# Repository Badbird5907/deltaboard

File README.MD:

# Deltaboard

Deltaboard is a TKL mechanical keyboard, directly using the [Keychron K8](https://www.keychron.com/products/keychron-k8-tenkeyless-wireless-mechanical-keyboard) as inspiration.
The hardest part building this project was routing all the switches and components for the RP2040.

[3D Render](https://autode.sk/4qxmMjt)

## Features:
- TKL Layout
- Kailh MX hotswap sockets
- OLED display
- Integrated RP2040
- USB-C
- RGB lighting
- EC11 Encoder
- QMK/VIA firmware

## Screenshots

### Schematic

### PCB

### Front

### Back

### Case

**Note:** 6mm standoffs are used to keep the keyboard properly fastened to the case. (The height of kailh hotswap sockets are around 5.5mm)

## BOM

| Name                      | Quantity | $ Total (USD) | Notes                                                                 | Links                                                                                                  |
|---------------------------|----------|---------------|-----------------------------------------------------------------------|--------------------------------------------------------------------------------------------------------|
| Cherry MX2A Brown RGB     | 84       | $35.92        | 90x, Free shipping (0.42c/switch)                                     | [Aliexpress](https://www.aliexpress.com/item/1005007917791662.html)                                    |
| DUROCK Stabilizer         | 1        | $8.74         | V3 BS 4x2u 1x6.25u                                                    | [Aliexpress](https://www.aliexpress.com/item/1005006528731543.html)                                    |
| M3 Heat Insert            | 1        | $2.39         | 50x, Free shipping                                                    | [Aliexpress](https://www.aliexpress.com/item/1005003582355741.html)                                    |
| M3 Standoffs (6mm)        | 1        | $2.02         | 50x, Free shipping                                                    | [Aliexpress](https://www.aliexpress.com/item/32539100523.html?spm=a2g0o.productlist.0.0.3351234eJmAx93) |
| M3 Screws (6mm)           | 1        | $1.94         | 50x, Free shipping                                                    | [Aliexpress](https://www.aliexpress.com/item/4001199728978.html)                                       |
| Wormier Pudding Keycaps   | 1        | $17.91        |                                                                       | [Amazon](https://www.amazon.ca/XVX-Keycaps-Universal-Compatiability-Keyboard/)                         |
| Kailh MX Hotswap Sockets  | 90       | $11.35        | 50x + 30x + 10x, Free shipping                                        | [Aliexpress](https://www.aliexpress.com/item/1005007225352311.html)                                    |
| I2C OLED Display (0.91")  | 1        | $2.25         | Free shipping                                                         | [Aliexpress](https://www.aliexpress.com/item/1005005301005280.html)                                    |
| EC11 Rotary Encoders      | 1        | $3.40         | 20mm Half Handle, Free shipping                                       | [Aliexpress](https://www.aliexpress.com/item/1005004907970664.html)                                    |
| Encoder Cap               | 1        | $2.23         | Half Handle Lid, Free shipping                                        | [Aliexpress](https://www.aliexpress.com/item/1005004907970664.html)                                    |
| LCSC Parts                | 1        | $27.33        | $12.47 total, $3 handling fee, $11.86 shipping. Covers MCU, diodes, LEDs | [BOM](https://github.com/Badbird5907/deltaboard/blob/master/Production/PCB/BOM-deltaboard.csv)         |
| PCB                       | 1        | $35.93        | $20.70 PCB + $15.23 shipping                                          |                                                                                                        |
**TOTAL: 151.41 USD**

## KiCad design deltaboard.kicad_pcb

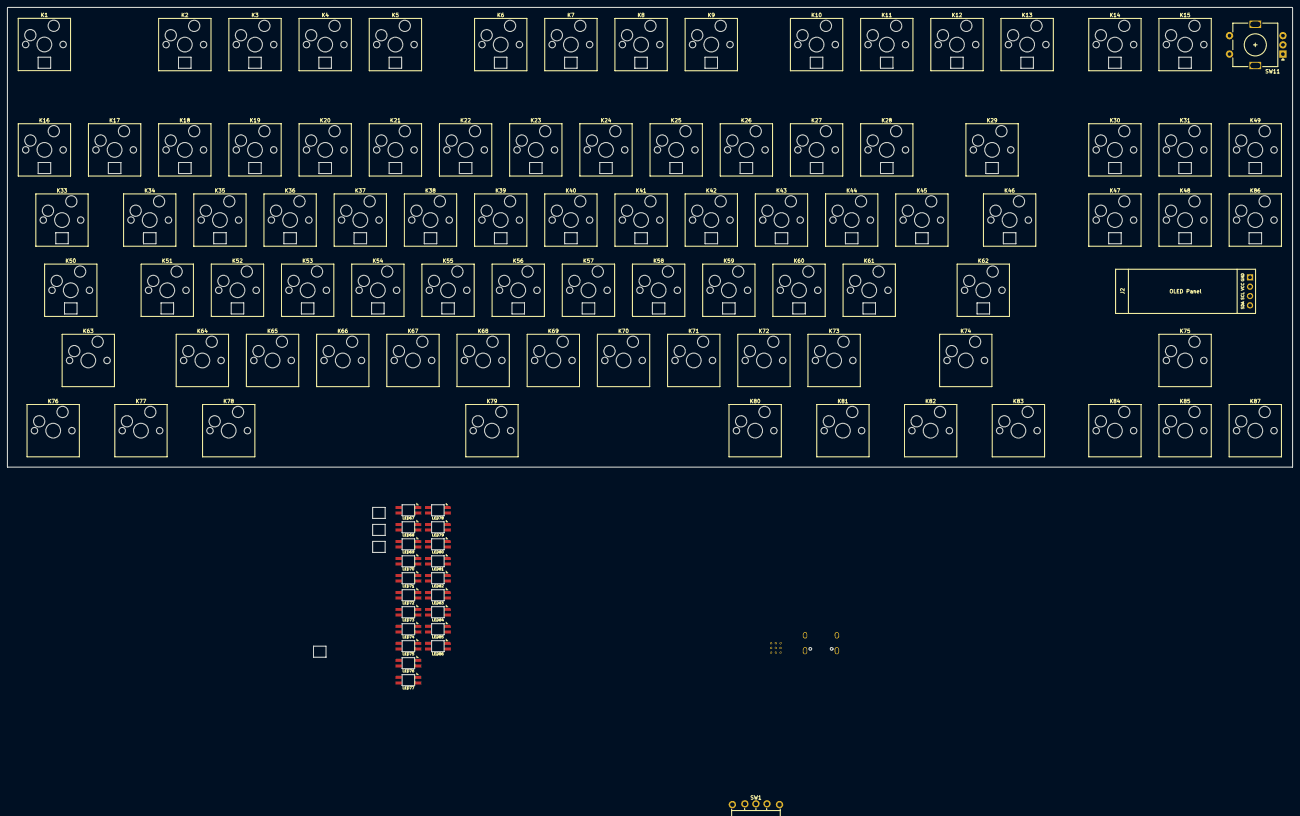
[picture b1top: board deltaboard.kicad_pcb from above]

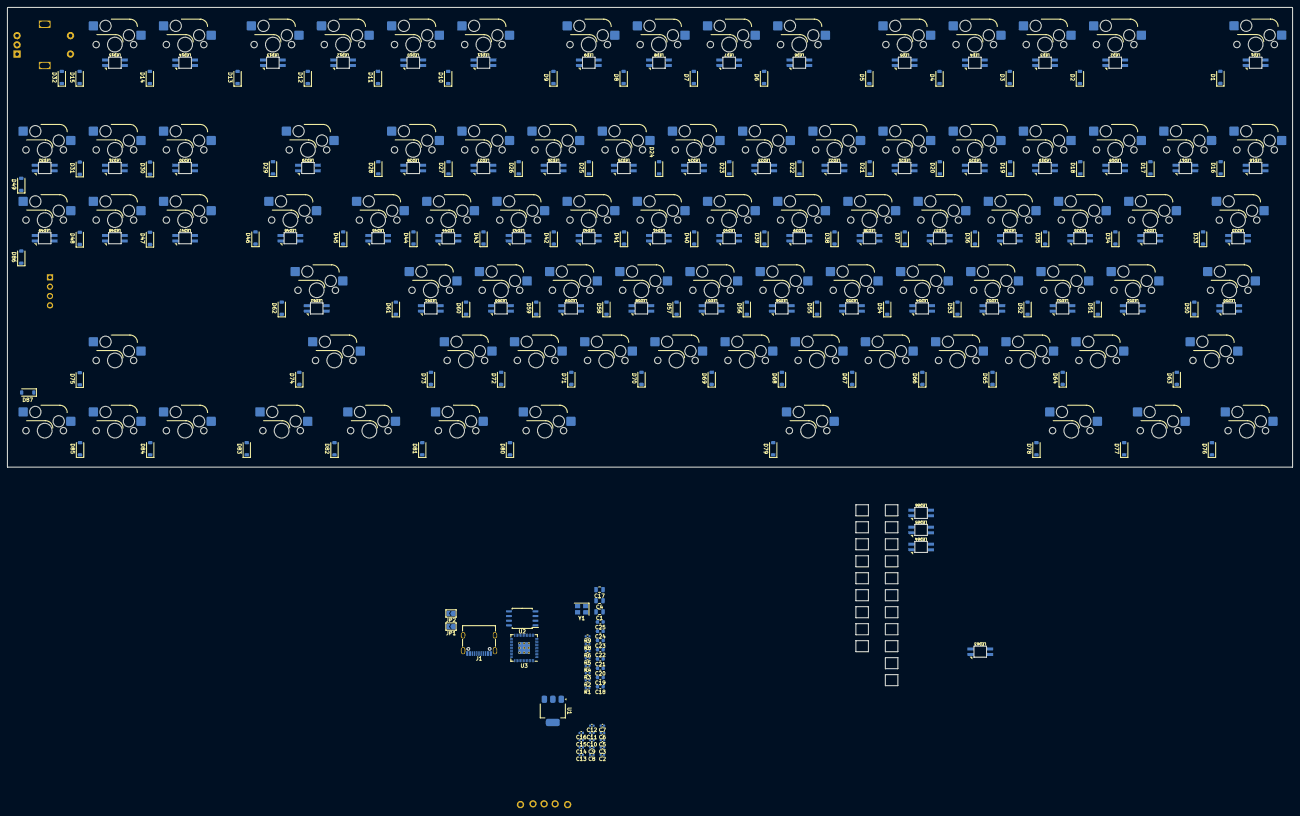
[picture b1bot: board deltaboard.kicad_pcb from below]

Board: 2 copper layers, 348.8 x 184.1 mm, 310 parts (193 on the bottom side), 224 nets, no tracks yet.

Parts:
C1, C4, C17: 10u; C_0805_2012Metric
C2, C3: 15p; C_0402_1005Metric
C5, C6, C7, C9, C11, C12, C13, C14, C15, C16: 100n; C_0402_1005Metric
C8, C10: 1u; C_0402_1005Metric
C18, C19, C20, C21, C22, C23, C24, C25: 2.2uF; C_0603_1608Metric
D1, D2, D3, D4, D5, D6, D7, D8, D9, D10, D11, D12, D13, D14, D15, D16, D17, D18, D19, D20, D21, D22, D23, D24, D25, D26, D27, D28, D29, D30, D31, D32, D33, D34, D35, D36, D37, D38, D39, D40, D41, D42, D43, D44, D45, D46, D47, D48, D49, D50, D51, D52, D53, D54, D55, D56, D57, D58, D59, D60, D61, D62, D63, D64, D65, D66, D67, D68, D69, D70, D71, D72, D73, D74, D75, D76, D77, D78, D79, D80, D81, D82, D83, D84, D85, D86, D87: D; D_SOD-123
H1, H2, H3, H4, H5, H6, H7, H8: MountingHole; MountingHole_2.7mm_M2.5
J1: USB_C_Receptacle; USB-C_SMD-TYPE-C-31-M-12
J2: Conn_01x04; SSD1306-0.91-OLED-4pin-128x32
JP1, JP2: Jumper_2_Open; SolderJumper-2_P1.3mm_Open_TrianglePad1.0x1.5mm
K1: Esc; Hotswap_MX_1.00u
K2: F1; Hotswap_MX_1.00u
K3: F2; Hotswap_MX_1.00u
K4: F3; Hotswap_MX_1.00u
K5: F4; Hotswap_MX_1.00u
K6: F5; Hotswap_MX_1.00u
K7: F6; Hotswap_MX_1.00u
K8: F7; Hotswap_MX_1.00u
K9: F8; Hotswap_MX_1.00u
K10: F9; Hotswap_MX_1.00u
K11: F10; Hotswap_MX_1.00u
K12: F11; Hotswap_MX_1.00u
K13: F12; Hotswap_MX_1.00u
K14, K15: Blank; Hotswap_MX_1.00u
K16: ~~,`; Hotswap_MX_1.00u
K17: !,1; Hotswap_MX_1.00u
K18: @,2; Hotswap_MX_1.00u
K19: #,3; Hotswap_MX_1.00u
K20: $,4; Hotswap_MX_1.00u
K21: %,5; Hotswap_MX_1.00u
K22: ^,6; Hotswap_MX_1.00u
K23: &,7; Hotswap_MX_1.00u
K24: *,8; Hotswap_MX_1.00u
K25: (,9; Hotswap_MX_1.00u
K26: ),0; Hotswap_MX_1.00u
K27: _,-; Hotswap_MX_1.00u
K28: +,=; Hotswap_MX_1.00u
K29: Backspace; Hotswap_MX_2.00u
K30: Insert; Hotswap_MX_1.00u
K31: Home; Hotswap_MX_1.00u
K33: Tab; Hotswap_MX_1.50u
K34: Q; Hotswap_MX_1.00u
K35: W; Hotswap_MX_1.00u
K36: E; Hotswap_MX_1.00u
K37: R; Hotswap_MX_1.00u
K38: T; Hotswap_MX_1.00u
K39: Y; Hotswap_MX_1.00u
K40: U; Hotswap_MX_1.00u
K41: I; Hotswap_MX_1.00u
K42: O; Hotswap_MX_1.00u
K43: P; Hotswap_MX_1.00u
K44: {,[; Hotswap_MX_1.00u
K45: },]; Hotswap_MX_1.00u
K46: |,\; Hotswap_MX_1.50u
K47: Delete; Hotswap_MX_1.00u
K48: End; Hotswap_MX_1.00u
K49: PgUp; Hotswap_MX_1.00u
K50: Caps Lock; Hotswap_MX_1.75u
K51: A; Hotswap_MX_1.00u
K52: S; Hotswap_MX_1.00u
K53: D; Hotswap_MX_1.00u
K54: F; Hotswap_MX_1.00u
K55: G; Hotswap_MX_1.00u
K56: H; Hotswap_MX_1.00u
K57: J; Hotswap_MX_1.00u
K58: K; Hotswap_MX_1.00u
K59: L; Hotswap_MX_1.00u
K60: :,;; Hotswap_MX_1.00u
K61: ",'; Hotswap_MX_1.00u
K62: Enter; Hotswap_MX_2.25u
K63: Shift; Hotswap_MX_2.25u
K64: Z; Hotswap_MX_1.00u
K65: X; Hotswap_MX_1.00u
K66: C; Hotswap_MX_1.00u
K67: V; Hotswap_MX_1.00u
K68: B; Hotswap_MX_1.00u
K69: N; Hotswap_MX_1.00u
K70: M; Hotswap_MX_1.00u
K71: <,,; Hotswap_MX_1.00u
K72: >,.; Hotswap_MX_1.00u
K73: ?,/; Hotswap_MX_1.00u
K74: Shift; Hotswap_MX_2.75u
K75: ↑; Hotswap_MX_1.00u
K76, K83: Ctrl; Hotswap_MX_1.25u
K77, K81: Win; Hotswap_MX_1.25u
K78, K80: Alt; Hotswap_MX_1.25u
K79: Blank; Hotswap_MX_6.25u
K82: Menu; Hotswap_MX_1.25u
K84: ←; Hotswap_MX_1.00u
K85: ↓; Hotswap_MX_1.00u
K86: PgDn; Hotswap_MX_1.00u
K87: →; Hotswap_MX_1.00u
LED1, LED2, LED3, LED4, LED5, LED6, LED7, LED8, LED9, LED10, LED11, LED12, LED13, LED14, LED15, LED16, LED17, LED18, LED19, LED20, LED21, LED22, LED23, LED24, LED25, LED26, LED27, LED28, LED29, LED30, LED31, LED32, LED33, LED34, LED35, LED36, LED37, LED38, LED39, LED40, LED41, LED42, LED43, LED44, LED45, LED46, LED47, LED48, LED49, LED50, LED51, LED52, LED53, LED54, LED55, LED56, LED57, LED58, LED59, LED60, LED61, LED62, LED63, LED64, LED65, LED66, LED67, LED68, LED69, LED70, LED71, LED72, LED73, LED74, LED75, LED76, LED77, LED78, LED79, LED80, LED81, LED82, LED83, LED84, LED85, LED86: SK6812-MINI-E; SK6812MINI-E
R1, R5, R6: 1k; R_0402_1005Metric
R2: DNF; R_0402_1005Metric
R3, R4: 27; R_0402_1005Metric
R8, R9: 5.1k; R_0402_1005Metric
SW1: SW_SPST; SW-TH_KH-SS12F23-G6
SW11: RotaryEncoder_Switch; encoder
U1: NCP1117-3.3_SOT223; SOT-223-3_TabPin2
U2: W25Q128JVS; SOIC-8_5.23x5.23mm_P1.27mm
U3: RP2040; RP2040-QFN-56
Y1: ABM8-272-T3; Crystal_SMD_3225-4Pin_3.2x2.5mm

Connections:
+1V1: C6.1, C7.1, C8.1, U3.23 (DVDD), U3.45 (VREG_VOUT), U3.50 (DVDD)
+3V3: C4.1, C5.1, C9.1, C10.1, C11.1, C12.1, C13.1, C14.1, C15.1, C16.1, C17.1, R2.1, U1.2 (VO), U2.8 (VCC), U3.1 (IOVDD), U3.10 (IOVDD), U3.22 (IOVDD), U3.33 (IOVDD), U3.42 (IOVDD), U3.43 (ADC_AVDD), U3.44 (VREG_IN), U3.48 (USB_VDD), U3.49 (IOVDD)
/COL_0: K1.1, K16.1, K33.1, K50.1, K63.1, K76.1, U3.8 (GPIO6)
/COL_1: K2.1, K17.1, K34.1, K51.1, K64.1, K77.1, U3.9 (GPIO7)
/COL_2: K3.1, K18.1, K35.1, K52.1, K65.1, K78.1, U3.11 (GPIO8)
/COL_3: K4.1, K19.1, K36.1, K53.1, K66.1, K79.1, U3.12 (GPIO9)
/COL_4: K5.1, K20.1, K37.1, K54.1, K67.1, K80.1, U3.13 (GPIO10)
/COL_5: K6.1, K21.1, K38.1, K55.1, K68.1, K81.1, U3.14 (GPIO11)
/COL_6: K7.1, K22.1, K39.1, K56.1, K69.1, K82.1, U3.15 (GPIO12)
/COL_7: K8.1, K23.1, K40.1, K57.1, K70.1, K83.1, U3.16 (GPIO13)
/COL_8: K9.1, K24.1, K41.1, K58.1, K71.1, K84.1, U3.17 (GPIO14)
/COL_9: K10.1, K25.1, K42.1, K59.1, K72.1, K85.1, U3.18 (GPIO15)
/COL_10: K11.1, K26.1, K43.1, K60.1, K73.1, K87.1, U3.27 (GPIO16)
/COL_11: K12.1, K27.1, K44.1, K61.1, K74.1, U3.28 (GPIO17)
/COL_12: K13.1, K28.1, K45.1, K62.1, K75.1, U3.29 (GPIO18)
/COL_13: K14.1, K29.1, K46.1, U3.30 (GPIO19)
/COL_14: K15.1, K30.1, K47.1, U3.31 (GPIO20)
/COL_16: K49.1, K86.1, U3.34 (GPIO22)
/GPIO0: D1.1 (K), D2.1 (K), D3.1 (K), D4.1 (K), D5.1 (K), D6.1 (K), D7.1 (K), D8.1 (K), D9.1 (K), D10.1 (K), D11.1 (K), D12.1 (K), D13.1 (K), D14.1 (K), D15.1 (K), D32.1 (K), U3.2 (GPIO0)
/GPIO1: D16.1 (K), D17.1 (K), D18.1 (K), D19.1 (K), D20.1 (K), D21.1 (K), D22.1 (K), D23.1 (K), D24.1 (K), D25.1 (K), D26.1 (K), D27.1 (K), D28.1 (K), D29.1 (K), D30.1 (K), D31.1 (K), D49.1 (K), U3.3 (GPIO1)
/GPIO2: D33.1 (K), D34.1 (K), D35.1 (K), D36.1 (K), D37.1 (K), D38.1 (K), D39.1 (K), D40.1 (K), D41.1 (K), D42.1 (K), D43.1 (K), D44.1 (K), D45.1 (K), D46.1 (K), D47.1 (K), D48.1 (K), D86.1 (K), U3.4 (GPIO2)
/GPIO3: D50.1 (K), D51.1 (K), D52.1 (K), D53.1 (K), D54.1 (K), D55.1 (K), D56.1 (K), D57.1 (K), D58.1 (K), D59.1 (K), D60.1 (K), D61.1 (K), D62.1 (K), U3.5 (GPIO3)
/GPIO4: D63.1 (K), D64.1 (K), D65.1 (K), D66.1 (K), D67.1 (K), D68.1 (K), D69.1 (K), D70.1 (K), D71.1 (K), D72.1 (K), D73.1 (K), D74.1 (K), D75.1 (K), U3.6 (GPIO4)
/GPIO5: D76.1 (K), D77.1 (K), D78.1 (K), D79.1 (K), D80.1 (K), D81.1 (K), D82.1 (K), D83.1 (K), D84.1 (K), D85.1 (K), D87.1 (K), U3.7 (GPIO5)
/QSPI_SCLK: U2.6 (CLK), U3.52 (QSPI_SCLK)
/QSPI_SD0: U2.5 (DI(IO0)), U3.53 (QSPI_SD0)
/QSPI_SD1: U2.2 (DO(IO1)), U3.55 (QSPI_SD1)
/QSPI_SD2: U2.3 (IO2), U3.54 (QSPI_SD2)
/QSPI_SD3: U2.7 (IO3), U3.51 (QSPI_SD3)
/QSPI_SS: R1.1, R2.2, U2.1 (~CS), U3.56 (QSPI_SS)
/RUN: R6.2, U3.26 (RUN)
/USB_D+: J1.A6 (D+), R3.1
/USB_D-: J1.A7 (D-), R4.1
/XIN: C2.1, U3.20 (XIN), Y1.1
/XOUT: R5.1, U3.21 (XOUT)
/~USB_BOOT: JP1.2 (B), R1.2
ENC_1_A: SW11.A, U3.39 (GPIO27_ADC1)
ENC_1_B: SW11.B, U3.38 (GPIO26_ADC0)
ENC_SWA: D32.2 (A), SW11.S2
ENC_SWB: K31.1, K48.1, SW11.S1, U3.32 (GPIO21)
GND: C1.2, C2.2, C3.2, C4.2, C5.2, C6.2, C7.2, C8.2, C9.2, C10.2, C11.2, C12.2, C13.2, C14.2, C15.2, C16.2, C17.2, C18.2, C19.2, C20.2, C21.2, C22.2, C23.2, C24.2, C25.2, J1.A1 (GND), J1.A12 (GND), J1.B1 (GND), J1.B12 (GND), J2.1, JP1.1 (A), JP2.1 (A), LED1.2 (VSS), LED2.2 (VSS), LED3.2 (VSS), LED4.2 (VSS), LED5.2 (VSS), LED6.2 (VSS), LED7.2 (VSS), LED8.2 (VSS), LED9.2 (VSS), LED10.2 (VSS), LED11.2 (VSS), LED12.2 (VSS), LED13.2 (VSS), LED14.2 (VSS), LED15.2 (VSS), LED16.2 (VSS), LED17.2 (VSS), LED18.2 (VSS), LED19.2 (VSS), LED20.2 (VSS), LED21.2 (VSS), LED22.2 (VSS), LED23.2 (VSS), LED24.2 (VSS), LED25.2 (VSS), LED26.2 (VSS), LED27.2 (VSS), LED28.2 (VSS), LED29.2 (VSS), LED30.2 (VSS), LED31.2 (VSS), LED32.2 (VSS), LED33.2 (VSS), LED34.2 (VSS), LED35.2 (VSS), LED36.2 (VSS), LED37.2 (VSS), LED38.2 (VSS), LED39.2 (VSS), LED40.2 (VSS), LED41.2 (VSS), LED42.2 (VSS), LED43.2 (VSS), LED44.2 (VSS), LED45.2 (VSS), LED46.2 (VSS), LED47.2 (VSS), LED48.2 (VSS), LED49.2 (VSS), LED50.2 (VSS), LED51.2 (VSS), LED52.2 (VSS), LED53.2 (VSS), LED54.2 (VSS), LED55.2 (VSS), LED56.2 (VSS), LED57.2 (VSS), LED58.2 (VSS), LED59.2 (VSS), LED60.2 (VSS), LED61.2 (VSS), LED62.2 (VSS), LED63.2 (VSS), LED64.2 (VSS), LED65.2 (VSS), LED66.2 (VSS), LED67.2 (VSS), LED68.2 (VSS), LED69.2 (VSS), LED70.2 (VSS), LED71.2 (VSS), LED72.2 (VSS), LED73.2 (VSS), LED74.2 (VSS), LED75.2 (VSS), LED76.2 (VSS), LED77.2 (VSS), LED78.2 (VSS), LED79.2 (VSS), LED80.2 (VSS), LED81.2 (VSS), LED82.2 (VSS), LED83.2 (VSS), LED84.2 (VSS), LED85.2 (VSS), LED86.2 (VSS), R8.2, R9.2, SW11.C, U1.1 (GND), U2.4 (GND), U3.19 (TESTEN), U3.57 (GND), Y1.2, Y1.4
I2C_SCL: J2.3, U3.37 (GPIO25)
I2C_SDA: J2.4, U3.36 (GPIO24)
LED: LED1.3 (DIN), U3.35 (GPIO23)
LED_OUT_0: LED15.1 (DOUT), LED16.3 (DIN)
LED_OUT_1: LED32.1 (DOUT), LED33.3 (DIN)
LED_OUT_2: LED49.1 (DOUT), LED50.3 (DIN)
LED_OUT_3: LED62.1 (DOUT), LED63.3 (DIN)
LED_OUT_4: LED75.1 (DOUT), LED76.3 (DIN)
unnamed: C3.1, R5.2, Y1.3
unnamed: D1.2 (A), K1.2
unnamed: D2.2 (A), K2.2
unnamed: D3.2 (A), K3.2
unnamed: D4.2 (A), K4.2
unnamed: D5.2 (A), K5.2
unnamed: D6.2 (A), K6.2
unnamed: D7.2 (A), K7.2
unnamed: D8.2 (A), K8.2
unnamed: D9.2 (A), K9.2
unnamed: D10.2 (A), K10.2
unnamed: D11.2 (A), K11.2
unnamed: D12.2 (A), K12.2
unnamed: D13.2 (A), K13.2
unnamed: D14.2 (A), K14.2
unnamed: D15.2 (A), K15.2
unnamed: D16.2 (A), K16.2
unnamed: D17.2 (A), K17.2
unnamed: D18.2 (A), K18.2
unnamed: D19.2 (A), K19.2
unnamed: D20.2 (A), K20.2
unnamed: D21.2 (A), K21.2
unnamed: D22.2 (A), K22.2
unnamed: D23.2 (A), K23.2
unnamed: D24.2 (A), K24.2
unnamed: D25.2 (A), K25.2
unnamed: D26.2 (A), K26.2
unnamed: D27.2 (A), K27.2
unnamed: D28.2 (A), K28.2
unnamed: D29.2 (A), K29.2
unnamed: D30.2 (A), K30.2
unnamed: D31.2 (A), K31.2
unnamed: D33.2 (A), K33.2
unnamed: D34.2 (A), K34.2
unnamed: D35.2 (A), K35.2
unnamed: D36.2 (A), K36.2
unnamed: D37.2 (A), K37.2
unnamed: D38.2 (A), K38.2
unnamed: D39.2 (A), K39.2
unnamed: D40.2 (A), K40.2
unnamed: D41.2 (A), K41.2
unnamed: D42.2 (A), K42.2
unnamed: D43.2 (A), K43.2
unnamed: D44.2 (A), K44.2
unnamed: D45.2 (A), K45.2
unnamed: D46.2 (A), K46.2
unnamed: D47.2 (A), K47.2
unnamed: D48.2 (A), K48.2
unnamed: D49.2 (A), K49.2
unnamed: D50.2 (A), K50.2
unnamed: D51.2 (A), K51.2
unnamed: D52.2 (A), K52.2
unnamed: D53.2 (A), K53.2
unnamed: D54.2 (A), K54.2
unnamed: D55.2 (A), K55.2
unnamed: D56.2 (A), K56.2
unnamed: D57.2 (A), K57.2
unnamed: D58.2 (A), K58.2
unnamed: D59.2 (A), K59.2
unnamed: D60.2 (A), K60.2
unnamed: D61.2 (A), K61.2
unnamed: D62.2 (A), K62.2
unnamed: D63.2 (A), K63.2
unnamed: D64.2 (A), K64.2
unnamed: D65.2 (A), K65.2
unnamed: D66.2 (A), K66.2
unnamed: D67.2 (A), K67.2
unnamed: D68.2 (A), K68.2
unnamed: D69.2 (A), K69.2
unnamed: D70.2 (A), K70.2
unnamed: D71.2 (A), K71.2
unnamed: D72.2 (A), K72.2
unnamed: D73.2 (A), K73.2
unnamed: D74.2 (A), K74.2
unnamed: D75.2 (A), K75.2
unnamed: D76.2 (A), K76.2
unnamed: D77.2 (A), K77.2
unnamed: D78.2 (A), K78.2
unnamed: D79.2 (A), K79.2
unnamed: D80.2 (A), K80.2
unnamed: D81.2 (A), K81.2
unnamed: D82.2 (A), K82.2
unnamed: D83.2 (A), K83.2
unnamed: D84.2 (A), K84.2
unnamed: D85.2 (A), K85.2
unnamed: D86.2 (A), K86.2
unnamed: D87.2 (A), K87.2
unnamed: J1.A5 (CC1), R8.1
unnamed: J1.B5 (CC2), R9.1
unnamed: JP2.2 (B), R6.1
unnamed: LED1.1 (DOUT), LED2.3 (DIN)
unnamed: LED2.1 (DOUT), LED3.3 (DIN)
unnamed: LED3.1 (DOUT), LED4.3 (DIN)
unnamed: LED4.1 (DOUT), LED5.3 (DIN)
unnamed: LED5.1 (DOUT), LED6.3 (DIN)
unnamed: LED6.1 (DOUT), LED7.3 (DIN)
unnamed: LED7.1 (DOUT), LED8.3 (DIN)
unnamed: LED8.1 (DOUT), LED9.3 (DIN)
unnamed: LED9.1 (DOUT), LED10.3 (DIN)
unnamed: LED10.1 (DOUT), LED11.3 (DIN)
unnamed: LED11.1 (DOUT), LED12.3 (DIN)
unnamed: LED12.1 (DOUT), LED13.3 (DIN)
unnamed: LED13.1 (DOUT), LED14.3 (DIN)
unnamed: LED14.1 (DOUT), LED15.3 (DIN)
unnamed: LED16.1 (DOUT), LED17.3 (DIN)
unnamed: LED17.1 (DOUT), LED18.3 (DIN)
unnamed: LED18.1 (DOUT), LED19.3 (DIN)
unnamed: LED19.1 (DOUT), LED20.3 (DIN)
unnamed: LED20.1 (DOUT), LED21.3 (DIN)
unnamed: LED21.1 (DOUT), LED22.3 (DIN)
unnamed: LED22.1 (DOUT), LED23.3 (DIN)
unnamed: LED23.1 (DOUT), LED24.3 (DIN)
unnamed: LED24.1 (DOUT), LED25.3 (DIN)
unnamed: LED25.1 (DOUT), LED26.3 (DIN)
unnamed: LED26.1 (DOUT), LED27.3 (DIN)
unnamed: LED27.1 (DOUT), LED28.3 (DIN)
unnamed: LED28.1 (DOUT), LED29.3 (DIN)
unnamed: LED29.1 (DOUT), LED30.3 (DIN)
unnamed: LED30.1 (DOUT), LED31.3 (DIN)
unnamed: LED31.1 (DOUT), LED32.3 (DIN)
unnamed: LED33.1 (DOUT), LED34.3 (DIN)
unnamed: LED34.1 (DOUT), LED35.3 (DIN)
unnamed: LED35.1 (DOUT), LED36.3 (DIN)
unnamed: LED36.1 (DOUT), LED37.3 (DIN)
unnamed: LED37.1 (DOUT), LED38.3 (DIN)
unnamed: LED38.1 (DOUT), LED39.3 (DIN)
unnamed: LED39.1 (DOUT), LED40.3 (DIN)
unnamed: LED40.1 (DOUT), LED41.3 (DIN)
unnamed: LED41.1 (DOUT), LED42.3 (DIN)
unnamed: LED42.1 (DOUT), LED43.3 (DIN)
unnamed: LED43.1 (DOUT), LED44.3 (DIN)
unnamed: LED44.1 (DOUT), LED45.3 (DIN)
unnamed: LED45.1 (DOUT), LED46.3 (DIN)
unnamed: LED46.1 (DOUT), LED47.3 (DIN)
unnamed: LED47.1 (DOUT), LED48.3 (DIN)
unnamed: LED48.1 (DOUT), LED49.3 (DIN)
unnamed: LED50.1 (DOUT), LED51.3 (DIN)
unnamed: LED51.1 (DOUT), LED52.3 (DIN)
unnamed: LED52.1 (DOUT), LED53.3 (DIN)
unnamed: LED53.1 (DOUT), LED54.3 (DIN)
unnamed: LED54.1 (DOUT), LED55.3 (DIN)
unnamed: LED55.1 (DOUT), LED56.3 (DIN)
unnamed: LED56.1 (DOUT), LED57.3 (DIN)
unnamed: LED57.1 (DOUT), LED58.3 (DIN)
unnamed: LED58.1 (DOUT), LED59.3 (DIN)
unnamed: LED59.1 (DOUT), LED60.3 (DIN)
unnamed: LED60.1 (DOUT), LED61.3 (DIN)
unnamed: LED61.1 (DOUT), LED62.3 (DIN)
unnamed: LED63.1 (DOUT), LED64.3 (DIN)
unnamed: LED64.1 (DOUT), LED65.3 (DIN)
unnamed: LED65.1 (DOUT), LED66.3 (DIN)
unnamed: LED66.1 (DOUT), LED67.3 (DIN)
unnamed: LED67.1 (DOUT), LED68.3 (DIN)
unnamed: LED68.1 (DOUT), LED69.3 (DIN)
unnamed: LED69.1 (DOUT), LED70.3 (DIN)
unnamed: LED70.1 (DOUT), LED71.3 (DIN)
unnamed: LED71.1 (DOUT), LED72.3 (DIN)
unnamed: LED72.1 (DOUT), LED73.3 (DIN)
unnamed: LED73.1 (DOUT), LED74.3 (DIN)
unnamed: LED74.1 (DOUT), LED75.3 (DIN)
unnamed: LED76.1 (DOUT), LED77.3 (DIN)
unnamed: LED77.1 (DOUT), LED78.3 (DIN)
unnamed: LED78.1 (DOUT), LED79.3 (DIN)
unnamed: LED79.1 (DOUT), LED80.3 (DIN)
unnamed: LED80.1 (DOUT), LED81.3 (DIN)
unnamed: LED81.1 (DOUT), LED82.3 (DIN)
unnamed: LED82.1 (DOUT), LED83.3 (DIN)
unnamed: LED83.1 (DOUT), LED84.3 (DIN)
unnamed: LED84.1 (DOUT), LED85.3 (DIN)
unnamed: LED85.1 (DOUT), LED86.3 (DIN)
unnamed: J1.A4 (VBUS), J1.A9 (VBUS), J1.B4 (VBUS), J1.B9 (VBUS), SW1.1 (A)
unnamed: R4.2, U3.46 (USB_DM)
unnamed: R3.2, U3.47 (USB_DP)
VBUS: C1.1, SW1.2 (B), U1.3 (VI)
VCC: C18.1, C19.1, C20.1, C21.1, C22.1, C23.1, C24.1, C25.1, J2.2, LED1.4 (VDD), LED2.4 (VDD), LED3.4 (VDD), LED4.4 (VDD), LED5.4 (VDD), LED6.4 (VDD), LED7.4 (VDD), LED8.4 (VDD), LED9.4 (VDD), LED10.4 (VDD), LED11.4 (VDD), LED12.4 (VDD), LED13.4 (VDD), LED14.4 (VDD), LED15.4 (VDD), LED16.4 (VDD), LED17.4 (VDD), LED18.4 (VDD), LED19.4 (VDD), LED20.4 (VDD), LED21.4 (VDD), LED22.4 (VDD), LED23.4 (VDD), LED24.4 (VDD), LED25.4 (VDD), LED26.4 (VDD), LED27.4 (VDD), LED28.4 (VDD), LED29.4 (VDD), LED30.4 (VDD), LED31.4 (VDD), LED32.4 (VDD), LED33.4 (VDD), LED34.4 (VDD), LED35.4 (VDD), LED36.4 (VDD), LED37.4 (VDD), LED38.4 (VDD), LED39.4 (VDD), LED40.4 (VDD), LED41.4 (VDD), LED42.4 (VDD), LED43.4 (VDD), LED44.4 (VDD), LED45.4 (VDD), LED46.4 (VDD), LED47.4 (VDD), LED48.4 (VDD), LED49.4 (VDD), LED50.4 (VDD), LED51.4 (VDD), LED52.4 (VDD), LED53.4 (VDD), LED54.4 (VDD), LED55.4 (VDD), LED56.4 (VDD), LED57.4 (VDD), LED58.4 (VDD), LED59.4 (VDD), LED60.4 (VDD), LED61.4 (VDD), LED62.4 (VDD), LED63.4 (VDD), LED64.4 (VDD), LED65.4 (VDD), LED66.4 (VDD), LED67.4 (VDD), LED68.4 (VDD), LED69.4 (VDD), LED70.4 (VDD), LED71.4 (VDD), LED72.4 (VDD), LED73.4 (VDD), LED74.4 (VDD), LED75.4 (VDD), LED76.4 (VDD), LED77.4 (VDD), LED78.4 (VDD), LED79.4 (VDD), LED80.4 (VDD), LED81.4 (VDD), LED82.4 (VDD), LED83.4 (VDD), LED84.4 (VDD), LED85.4 (VDD), LED86.4 (VDD)

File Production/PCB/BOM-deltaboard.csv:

Comment,Designator,Footprint,LCSC,Quantity
1k,"R1,R5,R6",R_0402_1005Metric,C11702,3
100n,"C11,C12,C13,C14,C15,C16,C5,C6,C7,C9",C_0402_1005Metric,C1525,10
15p,"C2,C3",C_0402_1005Metric,C1548,2
10u,"C1,C17,C4",C_0805_2012Metric,C15850,3
RP2040,U3,RP2040-QFN-56,C2040,1
ABM8-272-T3,Y1,Crystal_SMD_3225-4Pin_3.2x2.5mm,C20625731,1
2.2uF,"C18,C19,C20,C21,C22,C23,C24,C25",C_0603_1608Metric,C23630,8
27,"R3,R4",R_0402_1005Metric,C25100,2
5.1k,"R8,R9",R_0402_1005Metric,C25905,2
NCP1117-3.3_SOT223,U1,SOT-223-3_TabPin2,C26537,1
SK6812MINI-E,"LED1,LED10,LED11,LED12,LED13,LED14,LED15,LED16,LED17,LED18,LED19,LED2,LED20,LED21,LED22,LED23,LED24,LED25,LED26,LED27,LED28,LED29,LED3,LED30,LED31,LED32,LED33,LED34,LED35,LED36,LED37,LED38,LED39,LED4,LED40,LED41,LED42,LED43,LED44,LED45,LED46,LED47,LED48,LED49,LED5,LED50,LED51,LED52,LED53,LED54,LED55,LED56,LED57,LED58,LED59,LED6,LED60,LED61,LED62,LED63,LED64,LED65,LED66,LED67,LED68,LED69,LED7,LED70,LED71,LED72,LED73,LED74,LED75,LED76,LED77,LED78,LED79,LED8,LED80,LED81,LED82,LED83,LED84,LED85,LED86,LED9",SK6812MINI-E,C5149201,86
1u,"C10,C8",C_0402_1005Metric,C52923,2
USB_C_Receptacle,"J1,SW1",USB-C_SMD-TYPE-C-31-M-12,C7498220,2
D,"D1,D10,D11,D12,D13,D14,D15,D16,D17,D18,D19,D2,D20,D21,D22,D23,D24,D25,D26,D27,D28,D29,D3,D30,D31,D32,D33,D34,D35,D36,D37,D38,D39,D4,D40,D41,D42,D43,D44,D45,D46,D47,D48,D49,D5,D50,D51,D52,D53,D54,D55,D56,D57,D58,D59,D6,D60,D61,D62,D63,D64,D65,D66,D67,D68,D69,D7,D70,D71,D72,D73,D74,D75,D76,D77,D78,D79,D8,D80,D81,D82,D83,D84,D85,D86,D87,D9",D_SOD-123,C81598,87
W25Q128JVS,U2,SOIC-8_5.23x5.23mm_P1.27mm,C97521,1

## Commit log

2025-03-08 dhsuaj
2025-03-08 sajdashdjasdh
2025-03-09 add switches
2025-03-09 rename some labels
2025-03-09 fix: gitignore backups folder
2025-03-11 feat: add switches and leds
2025-03-11 update footprints
2025-03-11 feat: place most leds
2025-03-12 feat: start routing
2025-03-12 feat: set stab refs
2025-03-12 oops
2025-03-12 feat: finish placing components
2025-03-13 feat: finish most of the routing
2025-03-13 feat: finish routing!!
2025-03-13 fix: some minor cleanup
2025-03-13 chore: run cleanup tool
2025-03-13 chore: move pcb project to PCB/ folder
2025-03-13 feat: init qmk
2025-03-14 feat: work on qmk
2025-03-14 chore: update keyboard.json values
2025-03-14 feat: add readme
2025-03-14 feat: add screenshots
2025-03-14 feat: add images to readme
2025-03-14 feat: add via.json
2025-03-15 finalize pcb design
2025-03-15 feat: add more mounting holes
2025-03-15 optimize a bit more
2025-03-15 optimize one more trace
2025-03-15 optimize EVEN MORE TRACES
2025-03-15 generate initial production files
2025-03-15 add hole for oled to front plate
2025-03-15 add BOM.MD
2025-03-15 fix: set spacebar to 6.25u
2025-03-15 finish BOM
2025-03-19 fix: make build work and add build artifacts to production folder
2025-03-19 feat: add deltaboard silkscreen
2025-03-19 feat: brand pcb and case
2025-03-25 chore: remove kicad libraries
2025-03-25 add all.step
2025-04-20 chore: add i2c pull up resistors and make vcc traces thicker
2025-04-20 chore: properly connect DN/DP
2025-10-06 Replace HyperX Pudding Keycaps with Wormier Pudding Keycaps
2025-10-08 Add BOM.CSV
2025-10-08 Fix formatting issues in BOM.CSV
2025-10-08 Add PCB item with cost and shipping details
2025-10-08 Revise BOM totals and remove itemized costs
    Updated total costs and removed detailed breakdown of components.
2025-10-08 Clarify LCSC Parts description in BOM
    Updated LCSC Parts entry to clarify coverage of MCU and diodes/LEDs.
2025-10-08 Add BOM section to README
    Added a Bill of Materials (BOM) section with details on components, quantities, and costs.
2025-10-09 Replace case image with new render
    Updated the image for the 'Case' section in the README.
2025-10-09 Fix image file extension in README
2025-10-17 Update BOM with new item and total cost
2025-10-17 Add M3 Standoffs to BOM.CSV
2025-10-17 Fix BOM total and add note on standoffs
    Updated total cost in BOM section and added note about standoffs.
2025-10-17 Refactor BOM table and update shipping details
    Updated the BOM table format and corrected shipping notes.
2025-10-17 Revise BOM section in README
    Updated the Bill of Materials (BOM) section with corrected entries and formatting.
2025-12-04 feat: optimize traces, component placement, silkscreen, etc
2025-12-04 chore: remove accidentally created files
2025-12-05 feat: rework component placement + use different vrm fix bugs
2025-12-05 feat: hide footprint text for switches
2025-12-05 feat: use jetbrains mono font for diodes
2025-12-05 temp
2025-12-05 chore: cleanup
2025-12-05 chore: fix usb c footprint + symbol
2025-12-05 chore: source parts & generate prod files
2025-12-05 feat: move usb connector and switch back a bit
2025-12-05 chore: generate production files
2025-12-05 feat: round corners
2025-12-09 feat: use mosfet for switch
2025-12-09 chore: cleanup tracks
2025-12-09 feat: source parts & generate prod files
2025-12-09 fix: remove switches from bom
2025-12-09 feat: add stencil info to b.fab
2025-12-09 various changes
